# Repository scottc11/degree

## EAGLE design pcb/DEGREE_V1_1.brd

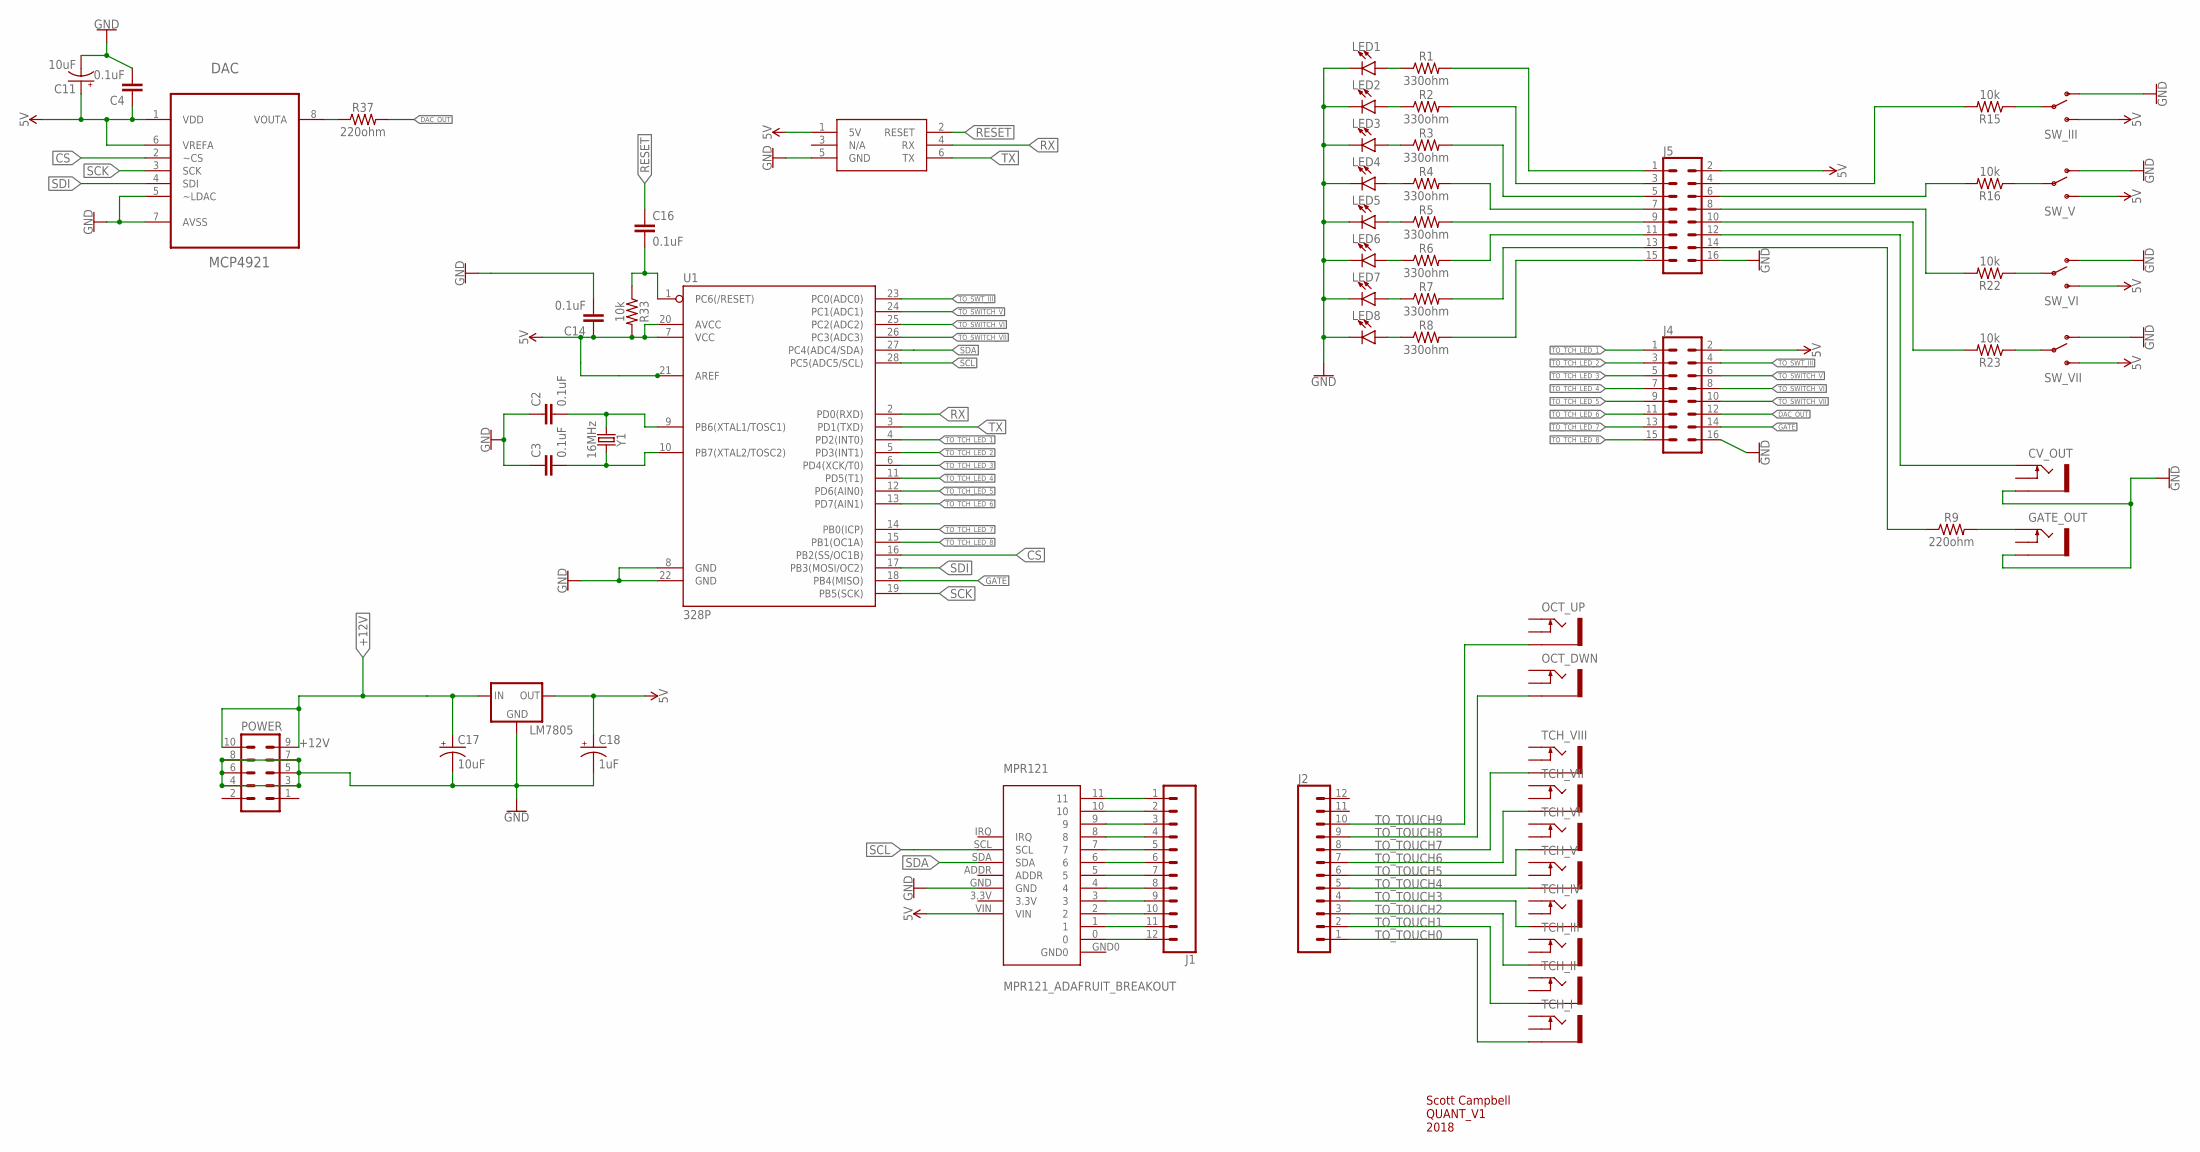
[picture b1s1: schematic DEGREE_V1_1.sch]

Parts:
C2, C3, C4, C14, C16: 0.1uF; CAP-PTH-SMALL-KIT
C11, C17: 10uF; CPOL-RADIAL-2.5MM-5MM
C18: 1uF; CPOL-RADIAL-2.5MM-5MM
CV_OUT: CV_OUT; WQP-PJ301M-12_JACK
DAC: MCP4921; DIP08
GATE_OUT: GATE_OUT; WQP-PJ301M-12_JACK
J1, J2: CONN_12; 1X12
J4, J5: CONN_08X2; 2X8
LED1, LED2, LED3, LED4, LED5, LED6, LED7, LED8: LED3MM; LED_3MM
LM7805: V_REG_78XXTO-92_UNTESTED; TO-92
MPR121: MPR121_ADAFRUIT_BREAKOUT
OCT_DWN: THONKICONN-ESSY
OCT_UP: THONKICONN-ESSY
POWER: EURO_POWER_HEADERREGULAR; EURO_POWER_HEADER
R1, R2, R3, R4, R5, R6, R7, R8: 330ohm; AXIAL-0.3
R9: 220ohm; HORIZONTAL_RESISTOR
R15, R16, R22, R23, R33: 10k; HORIZONTAL_RESISTOR
R37: 220ohm; VERTICAL_RESISTOR
SW_III: SUBMINI_SPDT; SUBMINI_TOGGLE
SW_V: SUBMINI_SPDT; SUBMINI_TOGGLE
SW_VI: SUBMINI_SPDT; SUBMINI_TOGGLE
SW_VII: SUBMINI_SPDT; SUBMINI_TOGGLE
TCH_I: THONKICONN-ESSY
TCH_II: THONKICONN-ESSY
TCH_III: THONKICONN-ESSY
TCH_IV: THONKICONN-ESSY
TCH_V: THONKICONN-ESSY
TCH_VI: THONKICONN-ESSY
TCH_VII: THONKICONN-ESSY
TCH_VIII: THONKICONN-ESSY
U1: 328P; DIP28
U$1: ATMEGA_PROGRAMMING_PINS
Y1: 16MHz; HC49US

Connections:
5V: C4.1, C11.1 (+), C14.1, C18.1 (+), DAC.1 (VDD), DAC.6 (VREFA), J4.2, J5.2, LM7805.1 (OUT), MPR121.VIN, R33.2, SW_III.3 (S), SW_V.3 (S), SW_VI.3 (S), SW_VII.3 (S), U1.7 (VCC), U1.20 (AVCC), U1.21 (AREF), U$1.1 (5V)
+12V: C17.1 (+), LM7805.3 (IN), POWER.9, POWER.10
CS: DAC.2 (~CS), U1.16 (PB2(SS/OC1B))
DAC_OUT: J4.12, R37.2
GATE: J4.14, U1.18 (PB4(MISO))
GND: C2.1, C3.1, C4.2, C11.2 (-), C14.2, C17.2 (-), C18.2 (-), CV_OUT.P$3_SLEEVE (SLEEVE), DAC.5 (~LDAC), DAC.7 (AVSS), GATE_OUT.P$3_SLEEVE (SLEEVE), J4.16, J5.16, LED1.K (C), LED2.K (C), LED3.K (C), LED4.K (C), LED5.K (C), LED6.K (C), LED7.K (C), LED8.K (C), LM7805.2 (GND), MPR121.GND, POWER.3, POWER.4, POWER.5, POWER.6, POWER.7, POWER.8, SW_III.1 (O), SW_V.1 (O), SW_VI.1 (O), SW_VII.1 (O), U1.8 (GND), U1.22 (GND), U$1.5 (GND)
unnamed: DAC.8 (VOUTA), R37.1
unnamed: GATE_OUT.P$1_TIP (TIP), R9.2
unnamed: R23.1, SW_VII.COM (COMMON)
unnamed: R22.1, SW_VI.COM (COMMON)
unnamed: R16.1, SW_V.COM (COMMON)
unnamed: R15.1, SW_III.COM (COMMON)
unnamed: C3.2, U1.10 (PB7(XTAL2/TOSC2)), Y1.2
unnamed: C2.2, U1.9 (PB6(XTAL1/TOSC1)), Y1.1
unnamed: J5.4, R15.2
unnamed: J5.6, R16.2
unnamed: J5.8, R22.2
unnamed: J1.1, MPR121.11
unnamed: J5.10, R23.2
unnamed: J1.2, MPR121.10
unnamed: J1.3, MPR121.9
unnamed: J1.4, MPR121.8
unnamed: J1.5, MPR121.7
unnamed: J1.6, MPR121.6
unnamed: J1.7, MPR121.5
unnamed: CV_OUT.P$1_TIP (TIP), J5.12
unnamed: J5.14, R9.1
unnamed: LED1.A, R1.P$1 (1)
unnamed: LED2.A, R2.P$1 (1)
unnamed: J1.8, MPR121.4
unnamed: J1.9, MPR121.3
unnamed: J1.10, MPR121.2
unnamed: J1.11, MPR121.1
unnamed: J1.12, MPR121.0
unnamed: LED3.A, R3.P$1 (1)
unnamed: LED4.A, R4.P$1 (1)
unnamed: LED5.A, R5.P$1 (1)
unnamed: LED6.A, R6.P$1 (1)
unnamed: LED7.A, R7.P$1 (1)
unnamed: LED8.A, R8.P$1 (1)
unnamed: C16.2, R33.1, U1.1 (PC6(/RESET))
RESET: C16.1, U$1.2 (RESET)
RX: U1.2 (PD0(RXD)), U$1.4 (RX)
SCK: DAC.3 (SCK), U1.19 (PB5(SCK))
SCL: MPR121.SCL, U1.28 (PC5(ADC5/SCL))
SDA: MPR121.SDA, U1.27 (PC4(ADC4/SDA))
SDI: DAC.4 (SDI), U1.17 (PB3(MOSI/OC2))
TCH_LED_1: J5.1, R1.P$2 (2)
TCH_LED_2: J5.3, R2.P$2 (2)
TCH_LED_3: J5.5, R3.P$2 (2)
TCH_LED_4: J5.7, R4.P$2 (2)
TCH_LED_5: J5.9, R5.P$2 (2)
TCH_LED_6: J5.11, R6.P$2 (2)
TCH_LED_7: J5.13, R7.P$2 (2)
TCH_LED_8: J5.15, R8.P$2 (2)
TO_SWITCH_V: J4.6, U1.24 (PC1(ADC1))
TO_SWITCH_VI: J4.8, U1.25 (PC2(ADC2))
TO_SWITCH_VII: J4.10, U1.26 (PC3(ADC3))
TO_SWT_III: J4.4, U1.23 (PC0(ADC0))
TO_TCH_LED_1: J4.1, U1.4 (PD2(INT0))
TO_TCH_LED_2: J4.3, U1.5 (PD3(INT1))
TO_TCH_LED_3: J4.5, U1.6 (PD4(XCK/T0))
TO_TCH_LED_4: J4.7, U1.11 (PD5(T1))
TO_TCH_LED_5: J4.9, U1.12 (PD6(AIN0))
TO_TCH_LED_6: J4.11, U1.13 (PD7(AIN1))
TO_TCH_LED_7: J4.13, U1.14 (PB0(ICP))
TO_TCH_LED_8: J4.15, U1.15 (PB1(OC1A))
TO_TOUCH0: J2.1, TCH_I.P$3_SLEEVE (SLEEVE)
TO_TOUCH1: J2.2, TCH_II.P$3_SLEEVE (SLEEVE)
TO_TOUCH2: J2.3, TCH_III.P$3_SLEEVE (SLEEVE)
TO_TOUCH3: J2.4, TCH_IV.P$3_SLEEVE (SLEEVE)
TO_TOUCH4: J2.5, TCH_V.P$3_SLEEVE (SLEEVE)
TO_TOUCH5: J2.6, TCH_VI.P$3_SLEEVE (SLEEVE)
TO_TOUCH6: J2.7, TCH_VII.P$3_SLEEVE (SLEEVE)
TO_TOUCH7: J2.8, TCH_VIII.P$3_SLEEVE (SLEEVE)
TO_TOUCH8: J2.9, OCT_DWN.P$3_SLEEVE (SLEEVE)
TO_TOUCH9: J2.10, OCT_UP.P$3_SLEEVE (SLEEVE)
TX: U1.3 (PD1(TXD)), U$1.6 (TX)

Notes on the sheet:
Scott Campbell QUANT_V1 2018

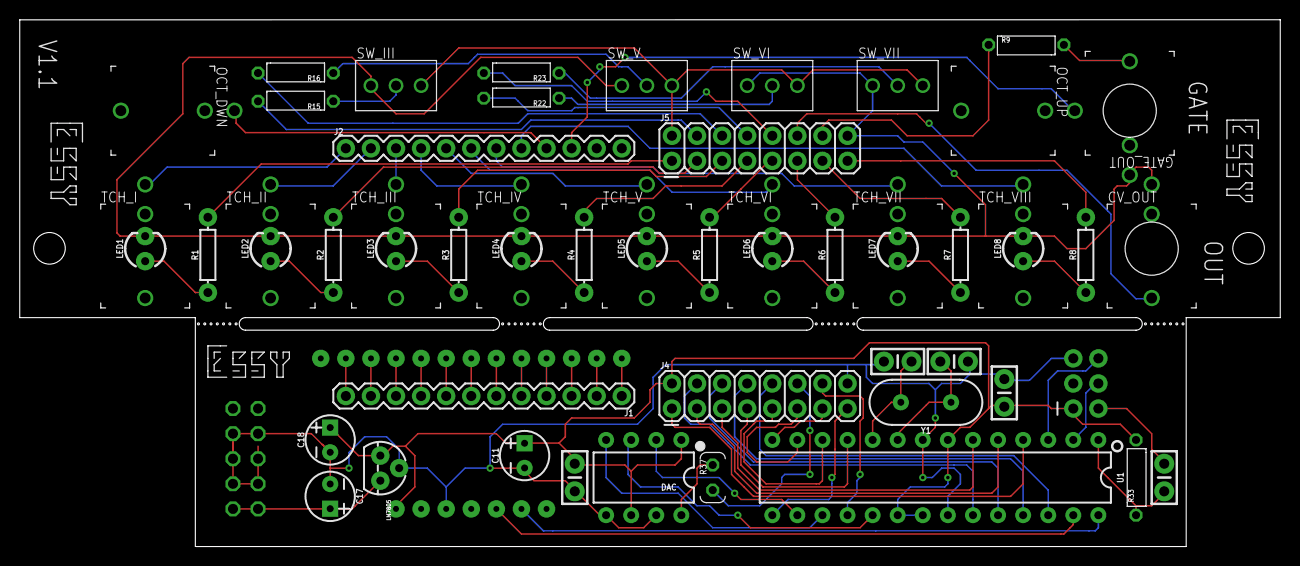
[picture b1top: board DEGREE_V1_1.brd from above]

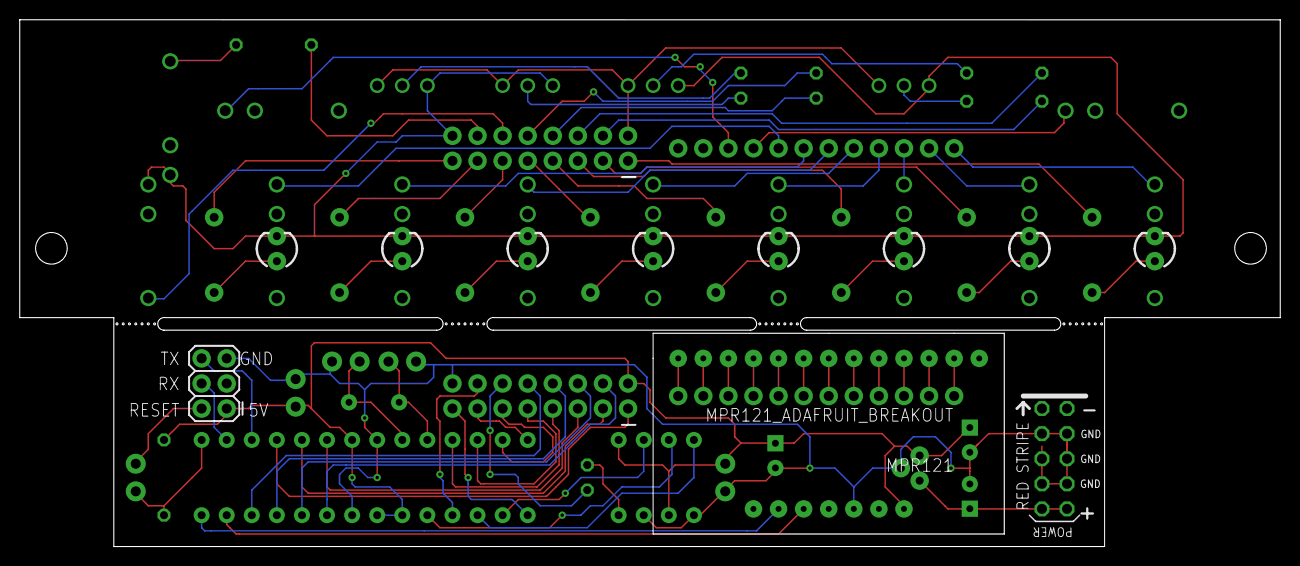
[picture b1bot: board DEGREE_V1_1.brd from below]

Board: 2 copper layers, 127.6 x 53.3 mm, 63 parts (3 on the bottom side), 78 nets.

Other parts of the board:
U$2, U$5, U$6: LOGO_SM
U$3, U$4: EURO_PANEL_SCREW_HOLE

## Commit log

2018-11-04 initial commit.
2018-11-04 fixed bug which defaulted non-switch degrees to wrong index.

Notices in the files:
parts and their libraries:
SparkFun-Capacitors: Licensing: Creative Commons ShareAlike 4.0 International - https://creativecommons.org/licenses/by-sa/4.0
